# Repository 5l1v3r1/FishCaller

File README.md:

FishCaller
==========

This is a simple circuit that will do short beeps at a few kHz. This should supposedly attract fish.

The inspiration is from this [fish calling kit](https://www.youtube.com/watch?v=3qwl95RwPuM)
and the circuit was adapted from this [alarm design](http://circuitdiagram.net/beeper-sound.html).

We will try and check if this works.

For more details on the project check the [Mediated
Landscape](http://wiki.biodesign.cc/wiki/Mediated_Landscapes) wiki page.

We are BIODESIGN for the REAL-WORLD and more info can be
found on our [wiki](http://wiki.biodesign.cc) and [blog](http://biodesign.cc).

Author
------

The PCB was laid quick and dirty by @fakufaku in April 2016.

License
-------

CC-BY-SA 3.0

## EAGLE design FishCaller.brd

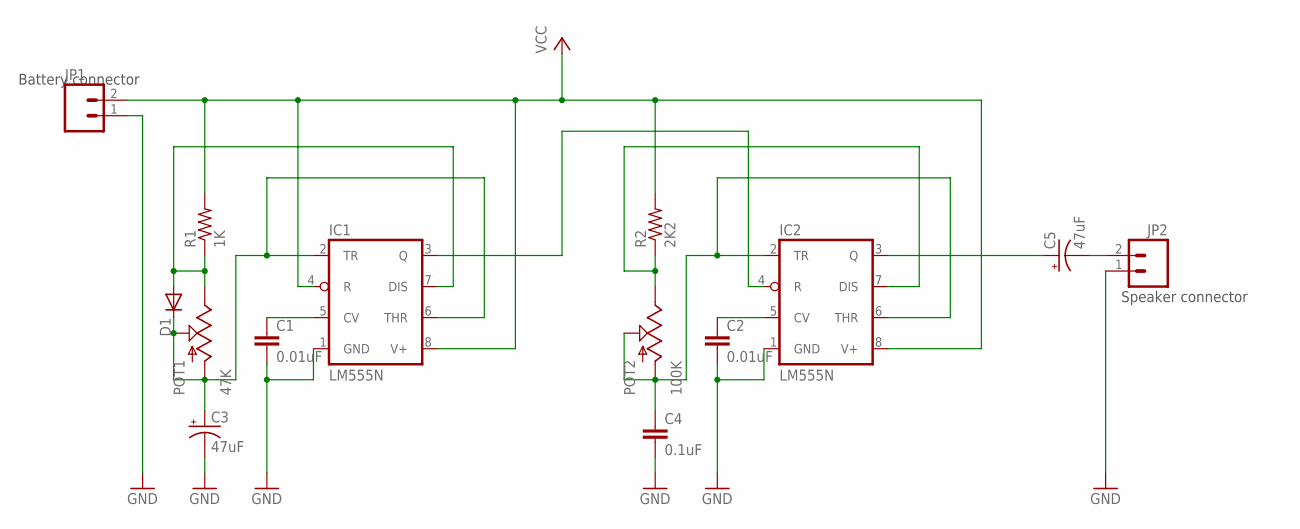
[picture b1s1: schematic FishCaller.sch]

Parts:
C1, C2: 0.01uF; CAP-PTH-SMALL
C3, C5: 47uF; E2,5-6
C4: 0.1uF; CAP-PTH-SMALL
D1: DIODE1N4148; DIODE-1N4148
IC1, IC2: LM555N; DIL08-ROUND
JP1, JP2: M02; 1X02_LONGPADS
POT1: 47K; ALPS_POT
POT2: 100K; ALPS_POT
R1: 1K; 0207/9
R2: 2K2; 0207/9

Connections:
GND: C1.2, C2.2, C3.-, C4.2, IC1.1 (GND), IC2.1 (GND), JP1.1, JP2.1
unnamed: C1.1, IC1.5 (CV)
unnamed: C2.1, IC2.5 (CV)
unnamed: IC2.7 (DIS), POT2.P$1 (E), R2.1
unnamed: C3.+, D1.C, IC1.2 (TR), IC1.6 (THR), POT1.P$2 (S), POT1.P$3 (A)
unnamed: D1.A, IC1.7 (DIS), POT1.P$1 (E), R1.1
unnamed: C5.+, IC2.3 (Q)
unnamed: C5.-, JP2.2
unnamed: C4.1, IC2.2 (TR), IC2.6 (THR), POT2.P$2 (S), POT2.P$3 (A)
unnamed: IC1.3 (Q), IC2.4 (R)
VCC: IC1.4 (R), IC1.8 (V+), IC2.8 (V+), JP1.2, R1.2, R2.2

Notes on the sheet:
Battery connector
Speaker connector

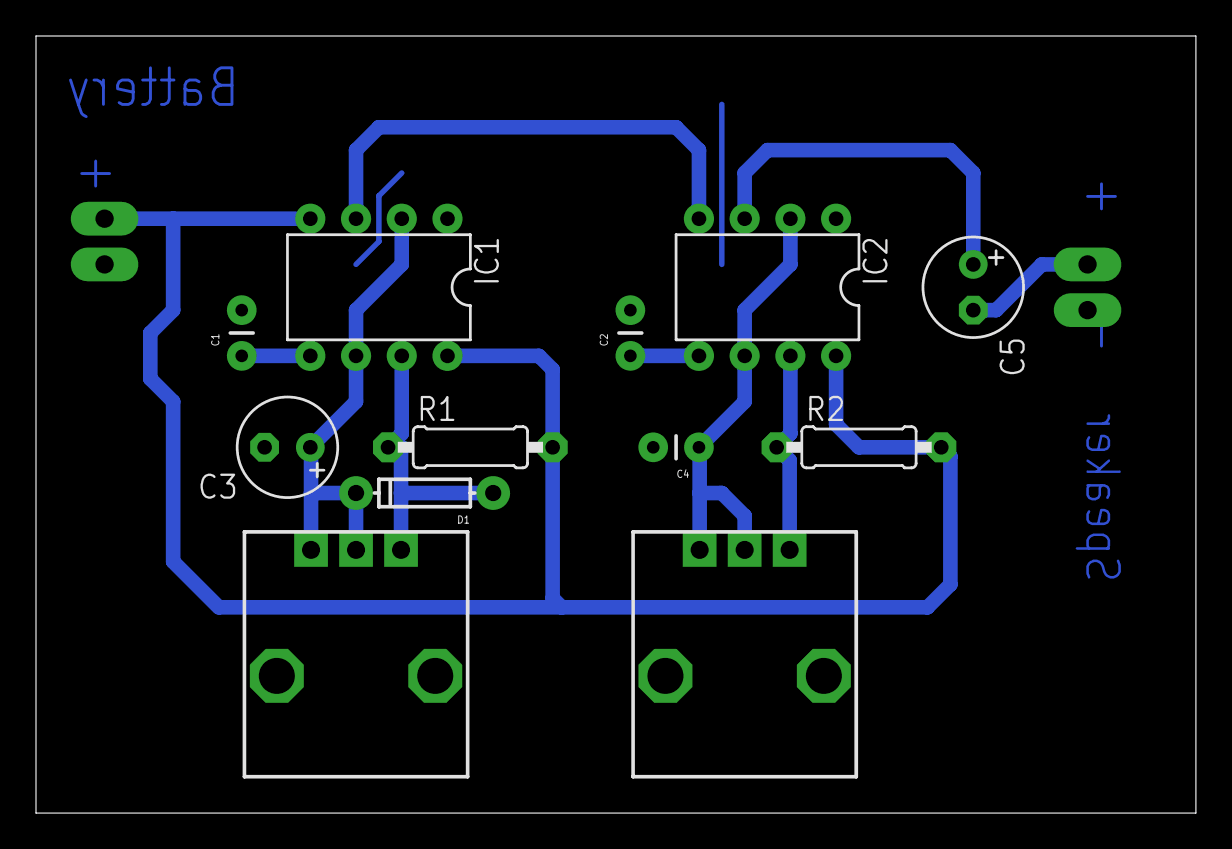
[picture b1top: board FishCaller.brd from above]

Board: 2 copper layers, 64.4 x 43.2 mm, 14 parts (0 on the bottom side), 11 nets.

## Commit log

2016-05-10 expanded README.
